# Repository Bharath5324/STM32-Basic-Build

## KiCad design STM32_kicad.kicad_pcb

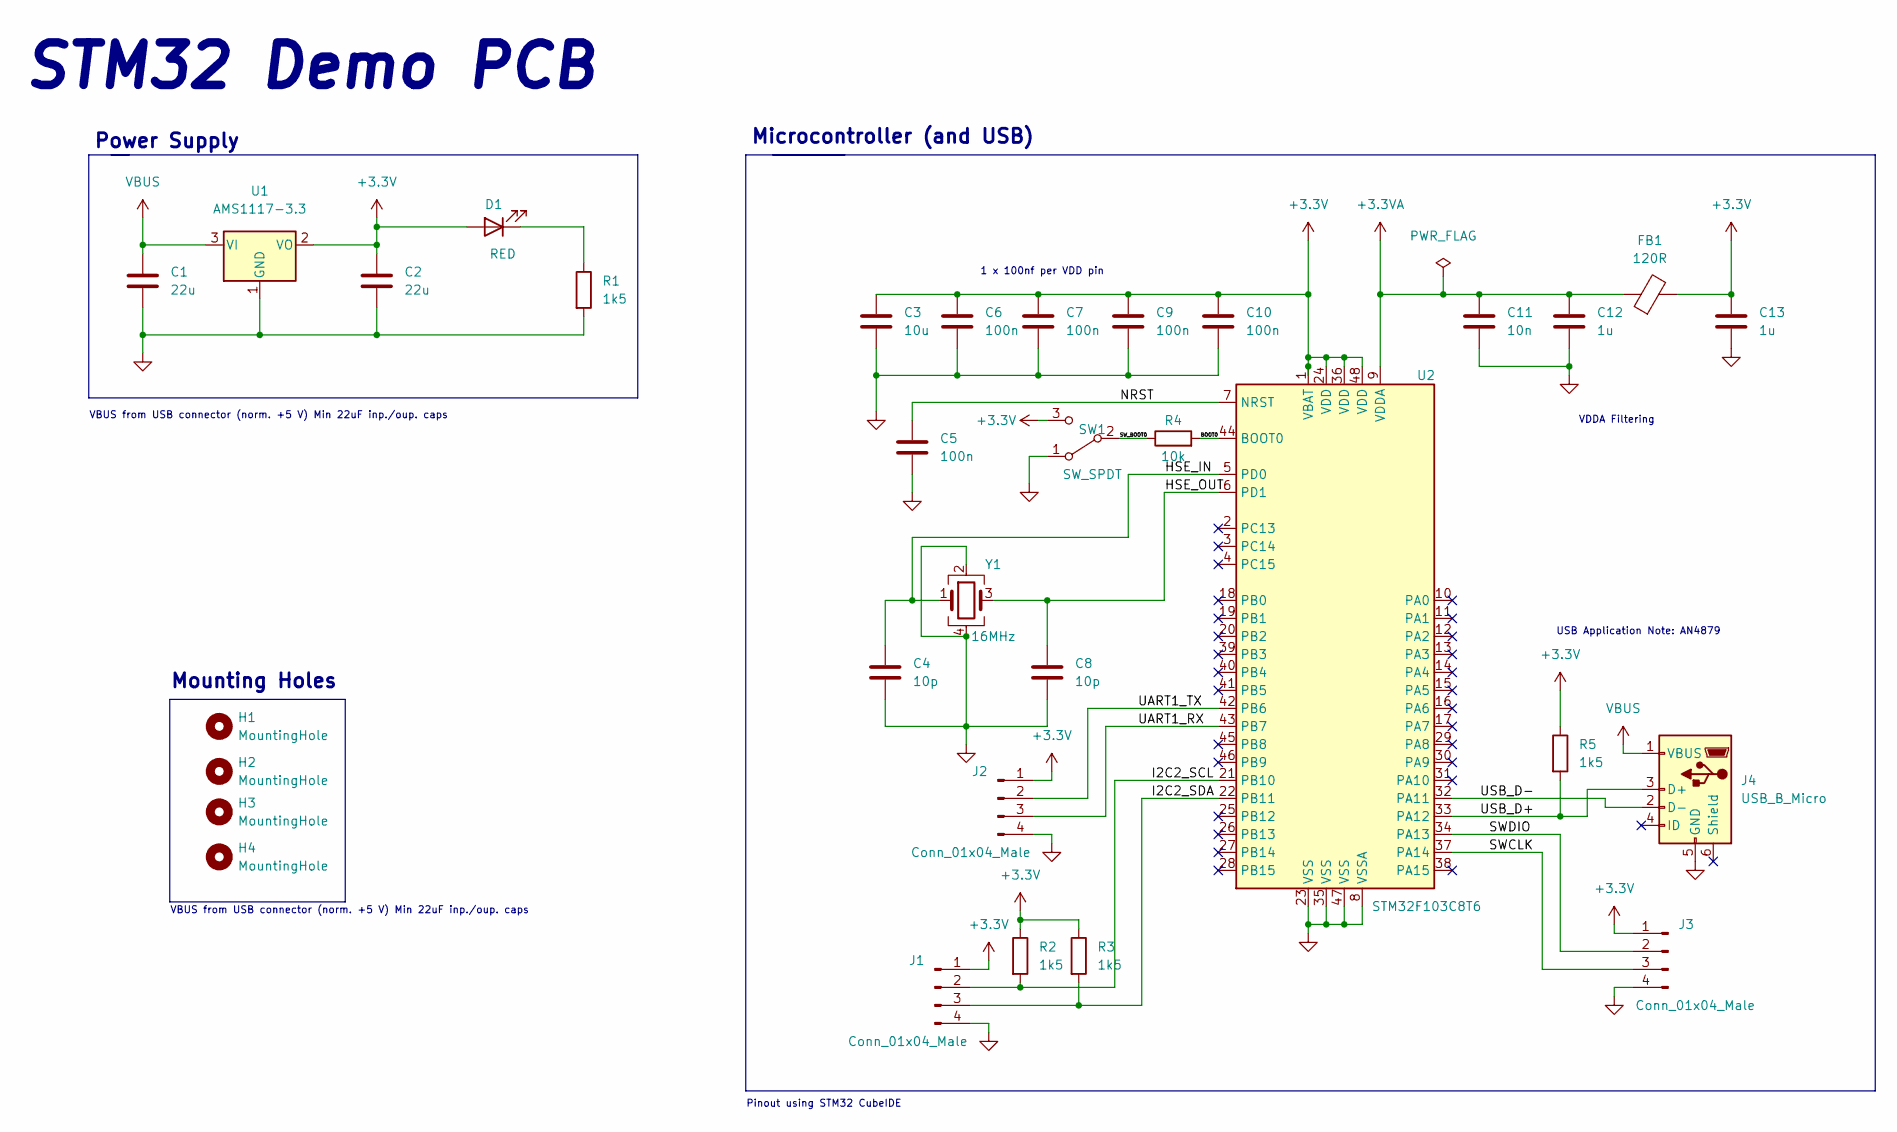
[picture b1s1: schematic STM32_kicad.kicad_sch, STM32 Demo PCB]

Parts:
C1, C2: 22u; C_0805_2012Metric
C3: 10u; C_0603_1608Metric
C4, C8: 10p; C_0402_1005Metric
C5, C6, C7, C9, C10: 100n; C_0402_1005Metric
C11: 10n; C_0402_1005Metric
C12, C13: 1u; C_0402_1005Metric
D1: RED; LED_0402_1005Metric
FB1: 120R; L_0603_1608Metric
H1, H2, H3, H4: MountingHole; MountingHole_2.1mm
J1, J2, J3: Conn_01x04_Male; PinHeader_1x04_P2.54mm_Vertical
J4: USB_B_Micro; USB_Micro-B_Wuerth_629105150521
R1, R2, R3, R5: 1k5; R_0402_1005Metric
R4: 10k; R_0402_1005Metric
SW1: SW_SPDT; SW_SPDT_PCM12
U1: AMS1117-3.3; SOT-223-3_TabPin2
U2: STM32F103C8T6; LQFP-48_7x7mm_P0.5mm
Y1: 16MHz; Crystal_SMD_3225-4Pin_3.2x2.5mm

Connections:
+3.3VA: C11.1, C12.1, FB1.1, U2.9 (VDDA)
+3V3: C2.1, C3.1, C6.1, C7.1, C9.1, C10.1, C13.1, D1.2 (A), FB1.2, J1.1, J2.1, J3.1, R2.1, R3.1, R5.1, SW1.3 (C), U1.2 (VO), U2.1 (VBAT), U2.24 (VDD), U2.36 (VDD), U2.48 (VDD)
/BOOT0: R4.2, U2.44 (BOOT0)
/HSE_IN: C4.1, U2.5 (PD0), Y1.1
/HSE_OUT: C8.1, U2.6 (PD1), Y1.3
/I2C2_SCL: J1.2, R2.2, U2.21 (PB10)
/I2C2_SDA: J1.3, R3.2, U2.22 (PB11)
/NRST: C5.1, U2.7 (NRST)
/SWCLK: J3.3, U2.37 (PA14)
/SWDIO: J3.2, U2.34 (PA13)
/SW_BOOT0: R4.1, SW1.2 (B)
/UART1_RX: J2.3, U2.43 (PB7)
/UART1_TX: J2.2, U2.42 (PB6)
/USB_D+: J4.3 (D+), R5.2, U2.33 (PA12)
/USB_D-: J4.2 (D-), U2.32 (PA11)
GND: C1.2, C2.2, C3.2, C4.2, C5.2, C6.2, C7.2, C8.2, C9.2, C10.2, C11.2, C12.2, C13.2, J1.4, J2.4, J3.4, J4.5 (GND), R1.2, SW1.1 (A), U1.1 (GND), U2.8 (VSSA), U2.23 (VSS), U2.35 (VSS), U2.47 (VSS), Y1.2, Y1.4
unnamed: D1.1 (K), R1.1
VBUS: C1.1, J4.1 (VBUS), U1.3 (VI)

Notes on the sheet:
VBUS from USB connector (norm. +5 V) Min 22uF inp./oup. caps
USB Application Note: AN4879
Power Supply
Mounting Holes
1 x 100nf per VDD pin
Microcontroller (and USB)
STM32 Demo PCB
Pinout using STM32 CubeIDE
VDDA Filtering

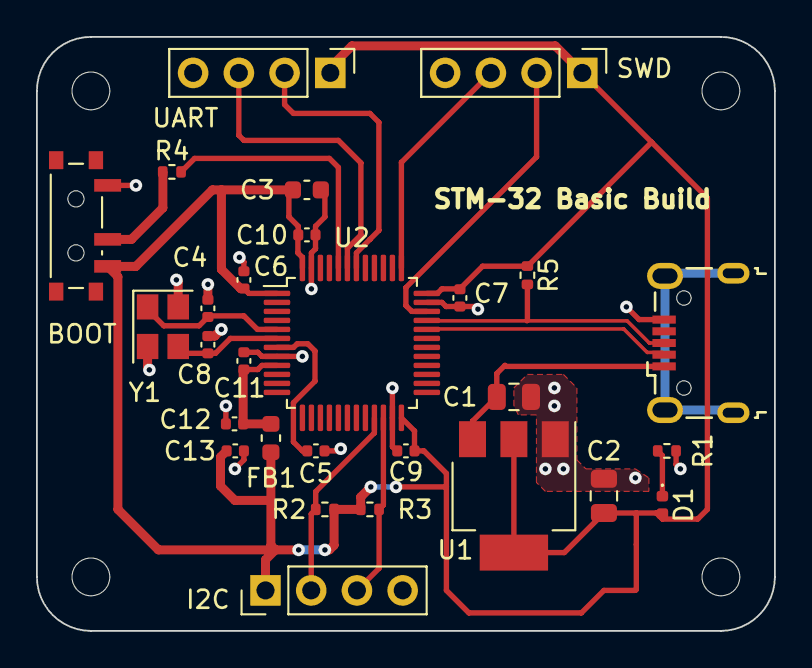
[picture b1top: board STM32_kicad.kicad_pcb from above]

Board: 2 copper layers, 41.0 x 33.0 mm, 32 parts (0 on the bottom side), 18 nets.

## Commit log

2023-02-13 final commit V1.0
